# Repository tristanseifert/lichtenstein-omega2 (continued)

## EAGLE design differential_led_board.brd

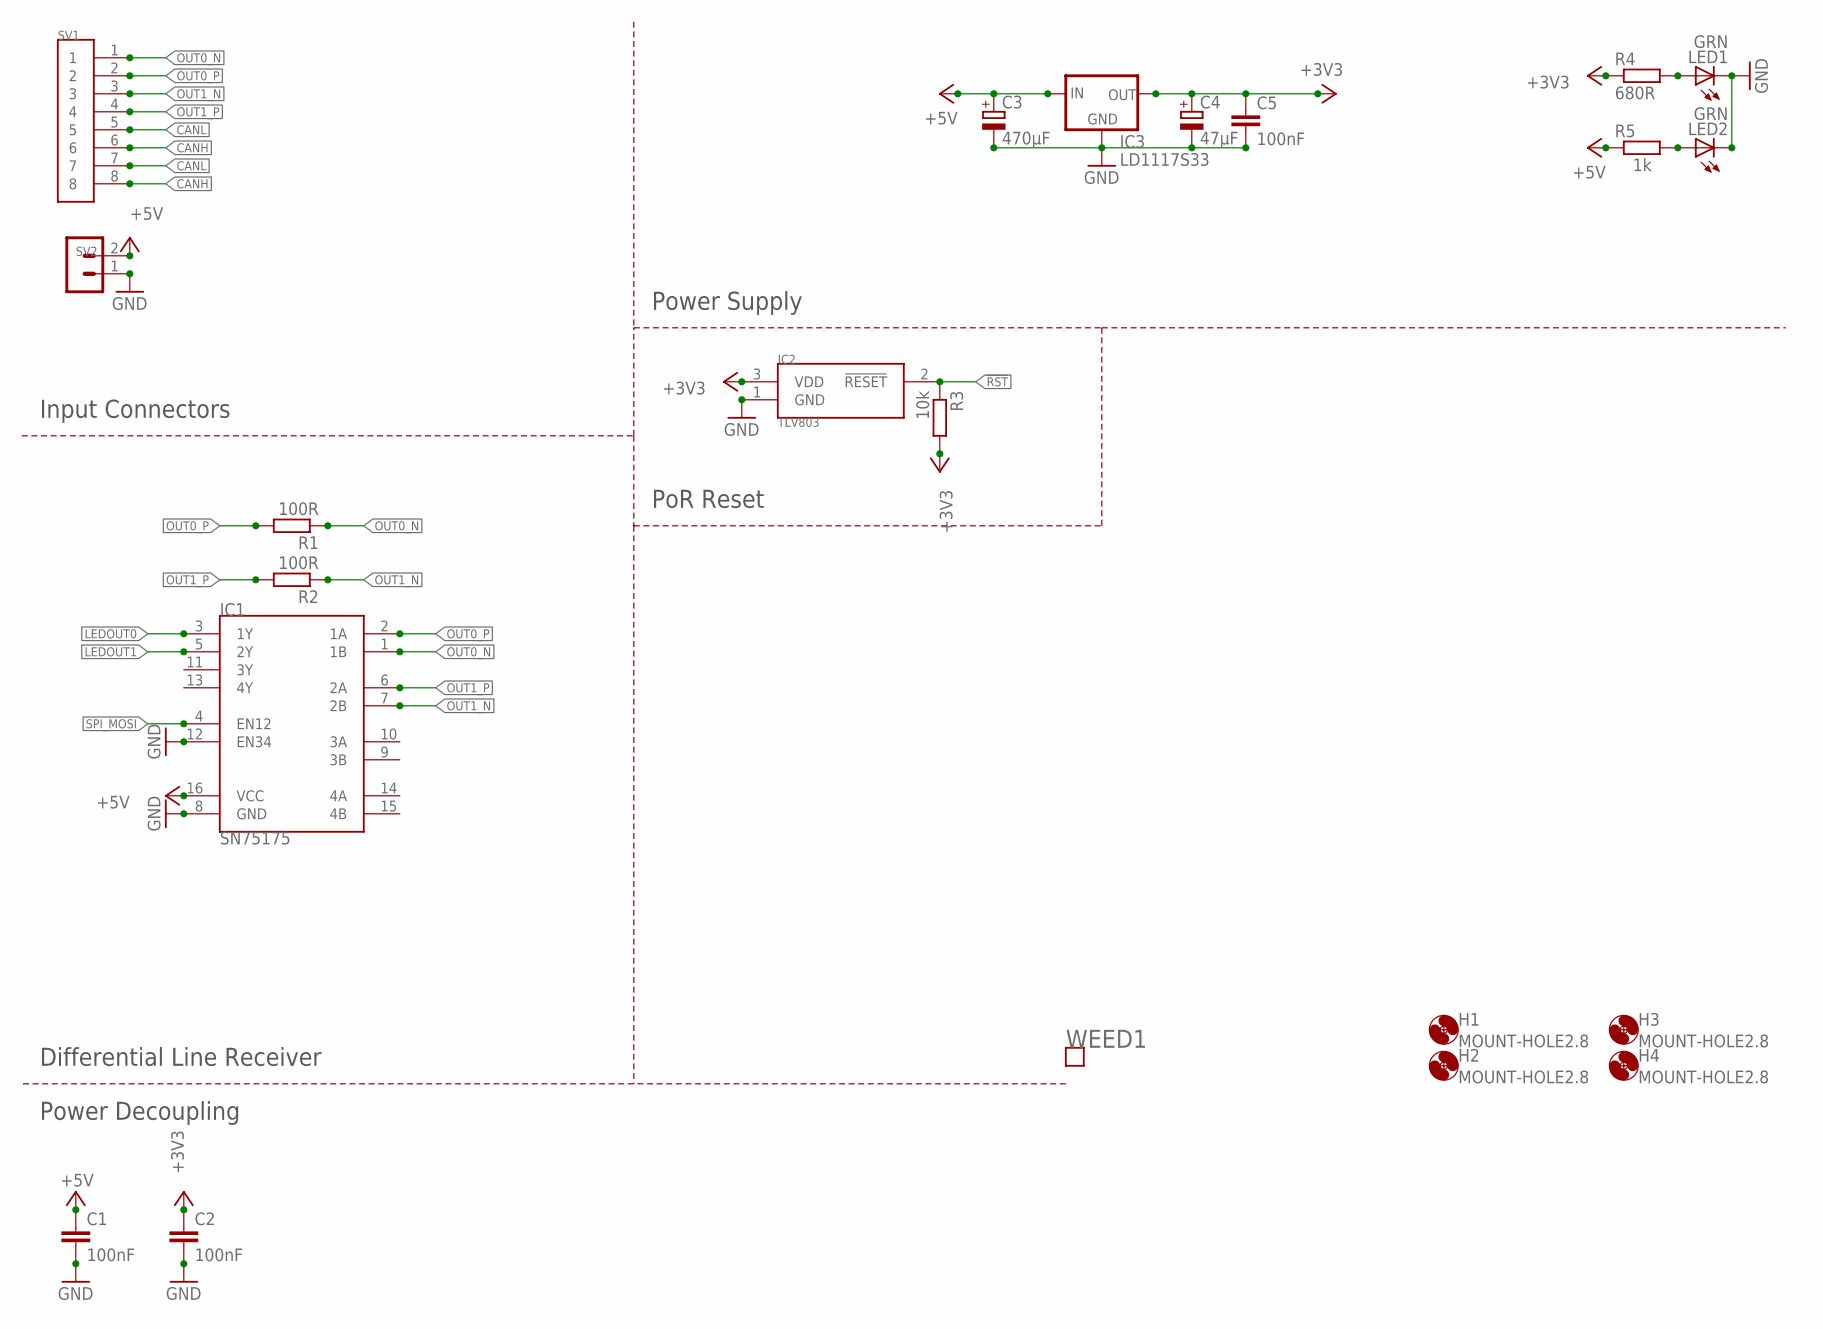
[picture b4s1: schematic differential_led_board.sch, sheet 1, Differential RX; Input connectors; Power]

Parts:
C1, C2, C5: 100nF; C0805; MOUSER 710-885012207072
C3: 470µF; UD-8X10_NICHICON; MOUSER 647-UWT1C471MNL1S
C4: 47µF; CT6032; MOUSER 581-TAJD476M016RNJV
H1, H2, H3, H4: MOUNT-HOLE2.8; 2,8
IC1: SN75175; SOP-16
IC2: TLV803; SOT23
IC3: LD1117S33; SOT223
LED1, LED2: GRN; CHIPLED_1206; MOUSER 604-APTR3216SGC
R1, R2: 100R; M1206; MOUSER 652-CR1206FX-1000ELF
R3: 10k; M0805; MOUSER 755-ESR10EZPJ103
R4: 680R; M0805; MOUSER 652-CR0805-FX6800GLF
R5: 1k; M0805; MOUSER 755-ESR10EZPJ102
SV1: SS-51000-003
SV2: 1792863
WEED1: WEED; DOINK

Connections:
!RST: IC2.2 (!RESET), R3.1; also elsewhere on the board
+3V3: C2.1, C4.+, C5.1, IC2.3 (VDD), IC3.2 (OUT), IC3.4 (OUT), R3.2, R4.1; also elsewhere on the board
+5V: C1.1, C3.+, IC1.16 (VCC), IC3.3 (IN), R5.1, SV2.2; also elsewhere on the board
CANH: SV1.6, SV1.8; also elsewhere on the board
CANL: SV1.5, SV1.7; also elsewhere on the board
GND: C1.2, C2.2, C3.-, C4.-, C5.2, IC1.8 (GND), IC1.12 (EN34), IC2.1 (GND), IC3.1 (GND), LED1.C, LED2.C, SV2.1; also elsewhere on the board
LEDOUT0: IC1.3 (1Y); also elsewhere on the board
LEDOUT1: IC1.5 (2Y); also elsewhere on the board
unnamed: LED1.A, R4.2
unnamed: LED2.A, R5.2
OUT0_N: IC1.1 (1B), R1.1, SV1.1
OUT0_P: IC1.2 (1A), R1.2, SV1.2
OUT1_N: IC1.7 (2B), R2.1, SV1.3
OUT1_P: IC1.6 (2A), R2.2, SV1.4
SPI_MOSI: IC1.4 (EN12); also elsewhere on the board

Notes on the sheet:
PoR Reset
Differential Line Receiver
Input Connectors
Power Supply
Power Decoupling

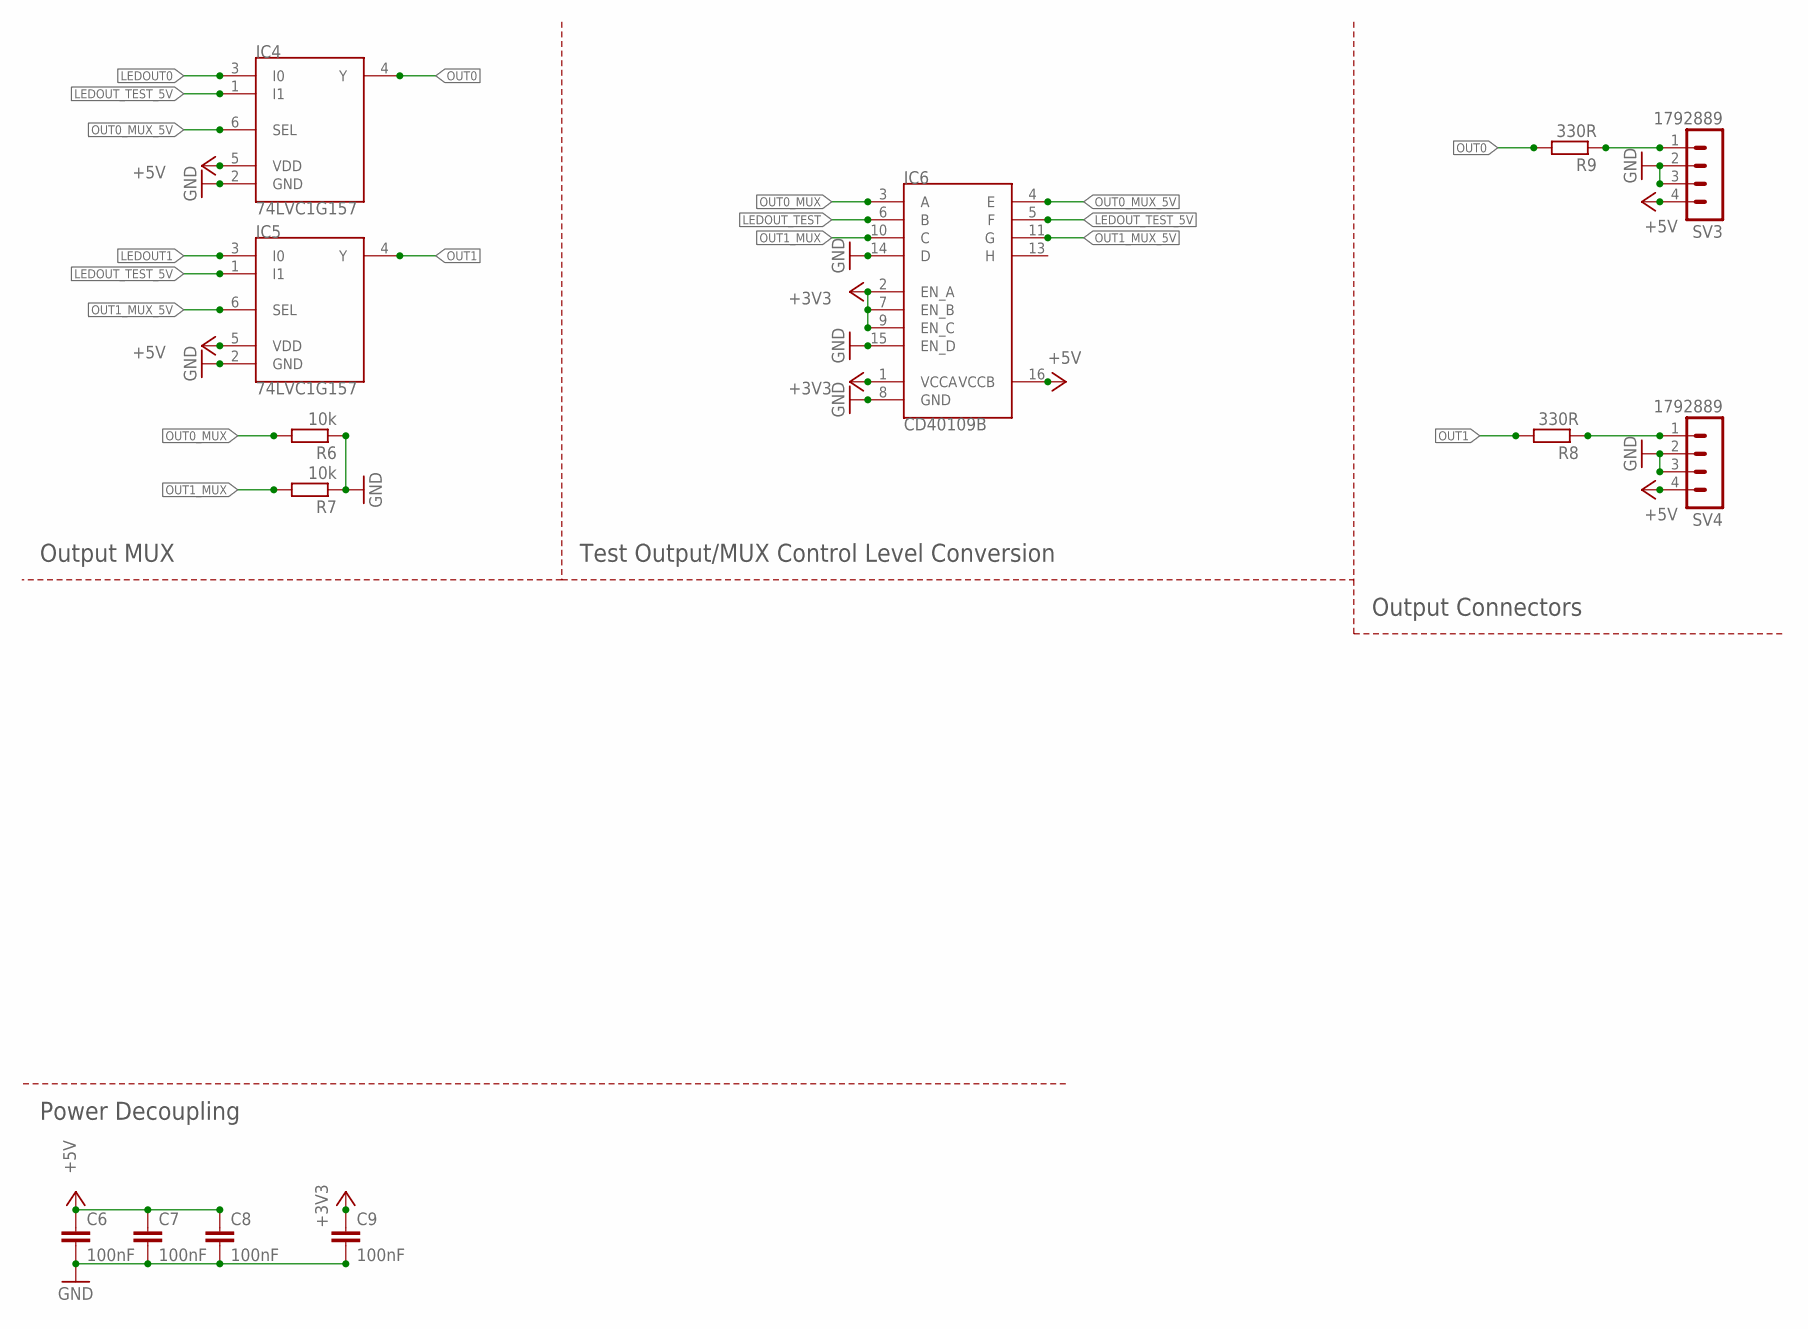
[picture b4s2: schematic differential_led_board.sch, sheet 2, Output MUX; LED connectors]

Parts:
C6, C7, C8, C9: 100nF; C0805; MOUSER 710-885012207072
IC4, IC5: 74LVC1G157; SOT457R_PHILIPS
IC6: CD40109B; SO16
R6, R7: 10k; M0805; MOUSER 755-ESR10EZPJ103
R8, R9: 330R; M0805; MOUSER 71-CRCW0805330RFKEAC
SV3, SV4: 1792889

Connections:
+3V3: C9.1, IC6.1 (VCCA), IC6.2 (EN_A), IC6.7 (EN_B), IC6.9 (EN_C); also elsewhere on the board
+5V: C6.1, C7.1, C8.1, IC4.5 (VDD), IC5.5 (VDD), IC6.16 (VCCB), SV3.4, SV4.4; also elsewhere on the board
GND: C6.2, C7.2, C8.2, C9.2, IC4.2 (GND), IC5.2 (GND), IC6.8 (GND), IC6.14 (D), IC6.15 (EN_D), R6.1, R7.1, SV3.2, SV3.3, SV4.2, SV4.3; also elsewhere on the board
LEDOUT0: IC4.3 (I0); also elsewhere on the board
LEDOUT1: IC5.3 (I0); also elsewhere on the board
LEDOUT_TEST: IC6.6 (B); also elsewhere on the board
LEDOUT_TEST_5V: IC4.1 (I1), IC5.1 (I1), IC6.5 (F)
unnamed: R8.1, SV4.1
unnamed: R9.1, SV3.1
OUT0: IC4.4 (Y), R9.2
OUT0_MUX: IC6.3 (A), R6.2; also elsewhere on the board
OUT0_MUX_5V: IC4.6 (SEL), IC6.4 (E)
OUT1: IC5.4 (Y), R8.2
OUT1_MUX: IC6.10 (C), R7.2; also elsewhere on the board
OUT1_MUX_5V: IC5.6 (SEL), IC6.11 (G)

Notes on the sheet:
Power Decoupling
Output Connectors
Output MUX
Test Output/MUX Control Level Conversion

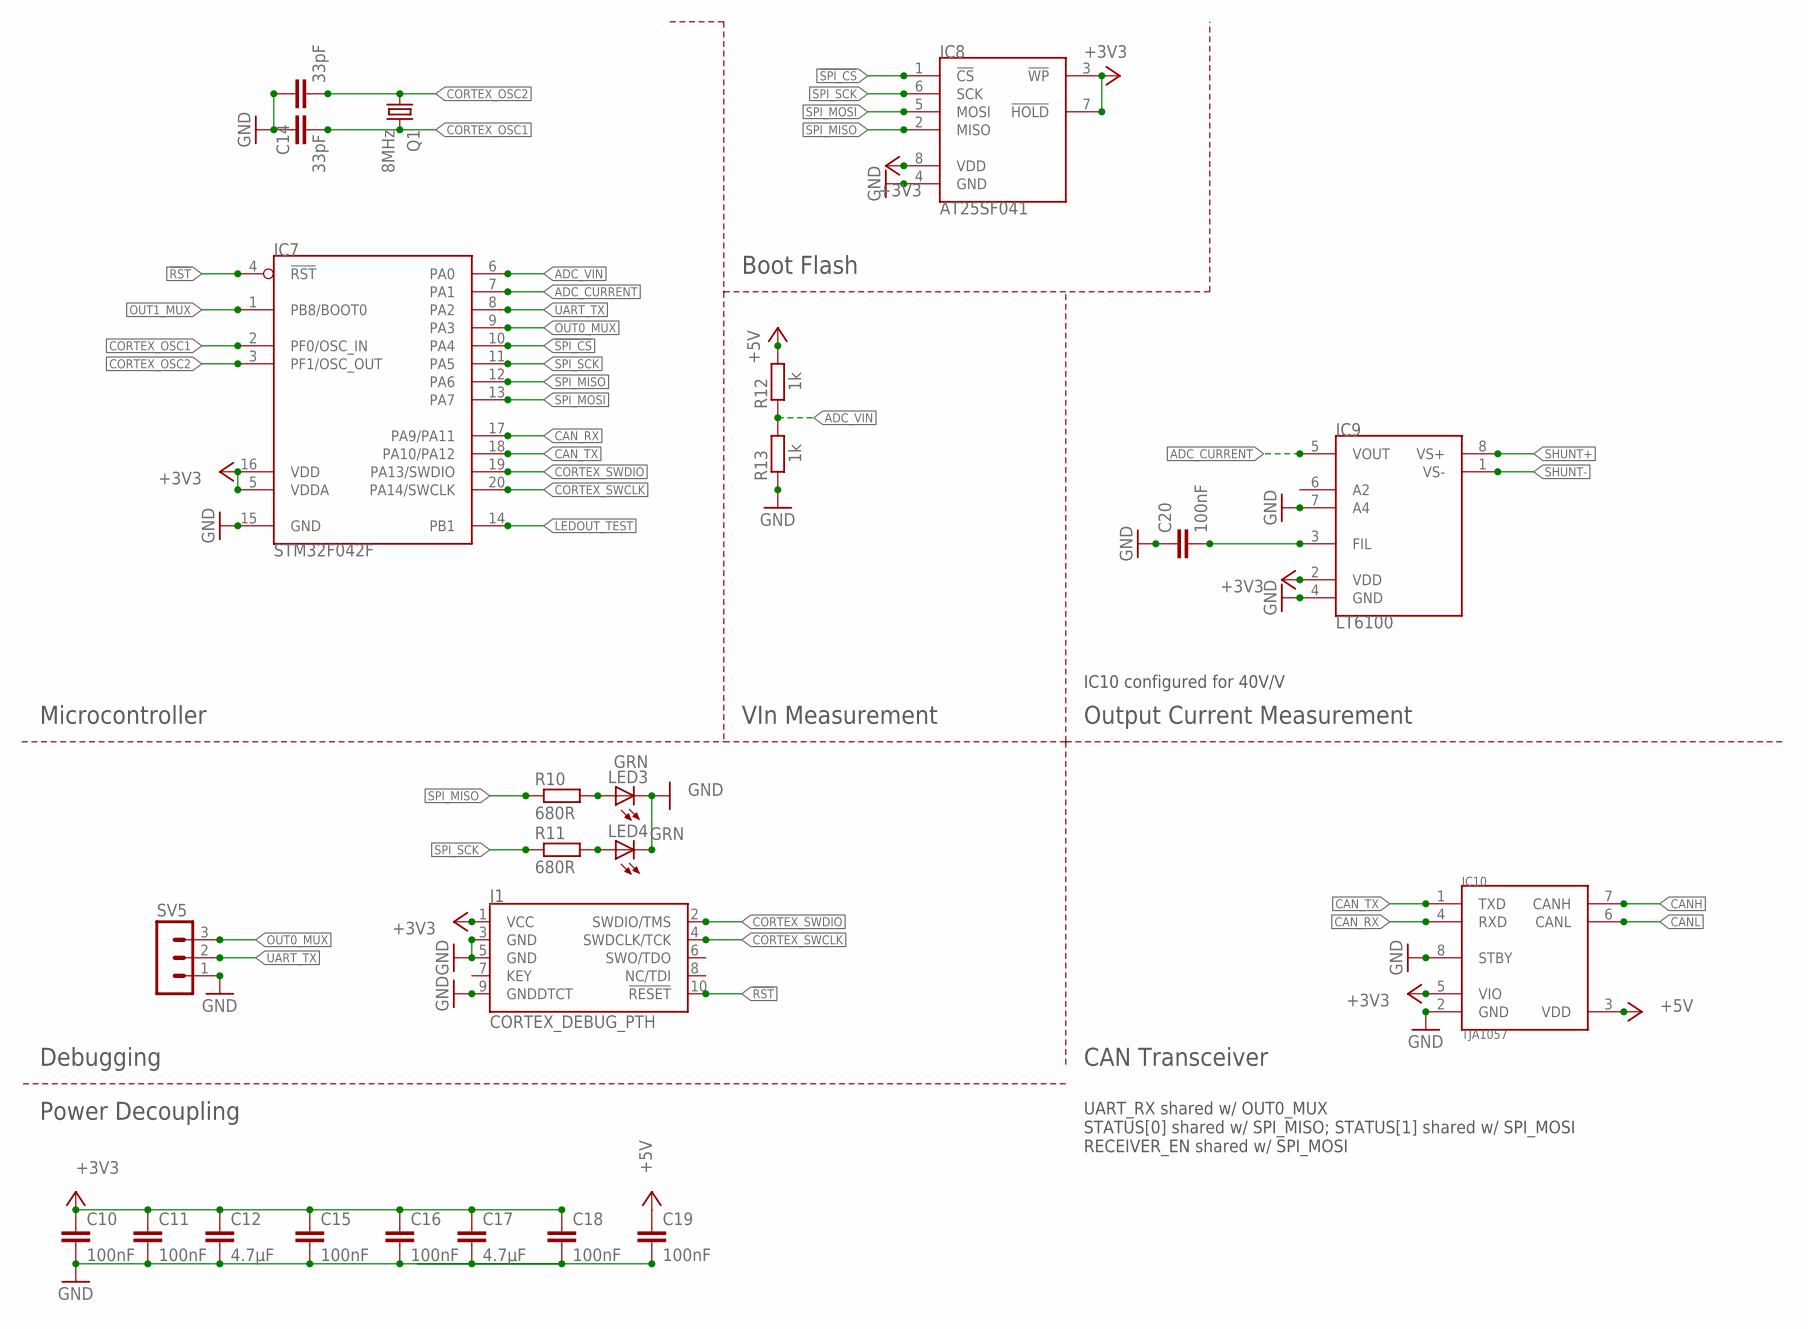
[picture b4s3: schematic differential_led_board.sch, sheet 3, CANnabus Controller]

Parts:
C10, C11, C15, C16, C18, C19: 100nF; C0805; MOUSER 710-885012207072
C12, C17: 4.7µF; C0805; MOUSER 81-GRM21BR71A475ME1L
C13, C14: 33pF; C0805; MOUSER 710-885012007013
C20: 100nF; C0805; MOUSER 710-885012007059
IC7: STM32F042F; TSSOP20
IC8: AT25SF041; SOIC8
IC9: LT6100; MSOP8
IC10: TJA1057; SOIC8
J1: CORTEX_DEBUG_PTH; 2X5-PTH-1.27MM
LED3, LED4: GRN; CHIPLED_1206; MOUSER 604-APTR3216SGC
Q1: 8MHz; HC49UP; MOUSER 449-LFXTAL030234REEL
R10, R11: 680R; M0805; MOUSER 652-CR0805-FX6800GLF
R12, R13: 1k; M0805; MOUSER 755-ESR10EZPJ102
SV5: MA03-1

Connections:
!RST: IC7.4 (!RST), J1.10 (!RESET); also elsewhere on the board
!SPI_CS: IC7.10 (PA4), IC8.1 (!CS)
+3V3: C10.1, C11.1, C12.1, C15.1, C16.1, C17.1, C18.1, IC7.5 (VDDA), IC7.16 (VDD), IC8.3 (!WP), IC8.7 (!HOLD), IC8.8 (VDD), IC9.2 (VDD), IC10.5 (VIO), J1.1 (VCC); also elsewhere on the board
+5V: C19.1, IC10.3 (VDD), R12.2; also elsewhere on the board
ADC_CURRENT: IC7.7 (PA1), IC9.5 (VOUT)
ADC_VIN: IC7.6 (PA0), R12.1, R13.2
CANH: IC10.7 (CANH); also elsewhere on the board
CANL: IC10.6 (CANL); also elsewhere on the board
CAN_RX: IC7.17 (PA9/PA11), IC10.4 (RXD)
CAN_TX: IC7.18 (PA10/PA12), IC10.1 (TXD)
CORTEX_OSC1: C14.2, IC7.2 (PF0/OSC_IN), Q1.2
CORTEX_OSC2: C13.2, IC7.3 (PF1/OSC_OUT), Q1.1
CORTEX_SWCLK: IC7.20 (PA14/SWCLK), J1.4 (SWDCLK/TCK)
CORTEX_SWDIO: IC7.19 (PA13/SWDIO), J1.2 (SWDIO/TMS)
GND: C10.2, C11.2, C12.2, C13.1, C14.1, C15.2, C16.2, C17.2, C18.2, C19.2, C20.1, IC7.15 (GND), IC8.4 (GND), IC9.4 (GND), IC9.7 (A4), IC10.2 (GND), IC10.8 (STBY), J1.3 (GND), J1.5 (GND), J1.9 (GNDDTCT), LED3.C, LED4.C, R13.1, SV5.1; also elsewhere on the board
LEDOUT_TEST: IC7.14 (PB1); also elsewhere on the board
unnamed: LED3.A, R10.2
unnamed: LED4.A, R11.2
unnamed: C20.2, IC9.3 (FIL)
OUT0_MUX: IC7.9 (PA3), SV5.3; also elsewhere on the board
OUT1_MUX: IC7.1 (PB8/BOOT0); also elsewhere on the board
SHUNT+: IC9.8 (VS+)
SHUNT-: IC9.1 (VS-)
SPI_MISO: IC7.12 (PA6), IC8.2 (MISO), R10.1
SPI_MOSI: IC7.13 (PA7), IC8.5 (MOSI); also elsewhere on the board
SPI_SCK: IC7.11 (PA5), IC8.6 (SCK), R11.1
UART_TX: IC7.8 (PA2), SV5.2

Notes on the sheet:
UART_RX shared w/ OUT0_MUX STATUS[0] shared w/ SPI_MISO; STATUS[1] shared w/ SPI_MOSI RECEIVER_EN shared w/ SPI_MOSI
Microcontroller
Debugging
Power Decoupling
CAN Transceiver
Boot Flash
VIn Measurement
Output Current Measurement
IC10 configured for 40V/V

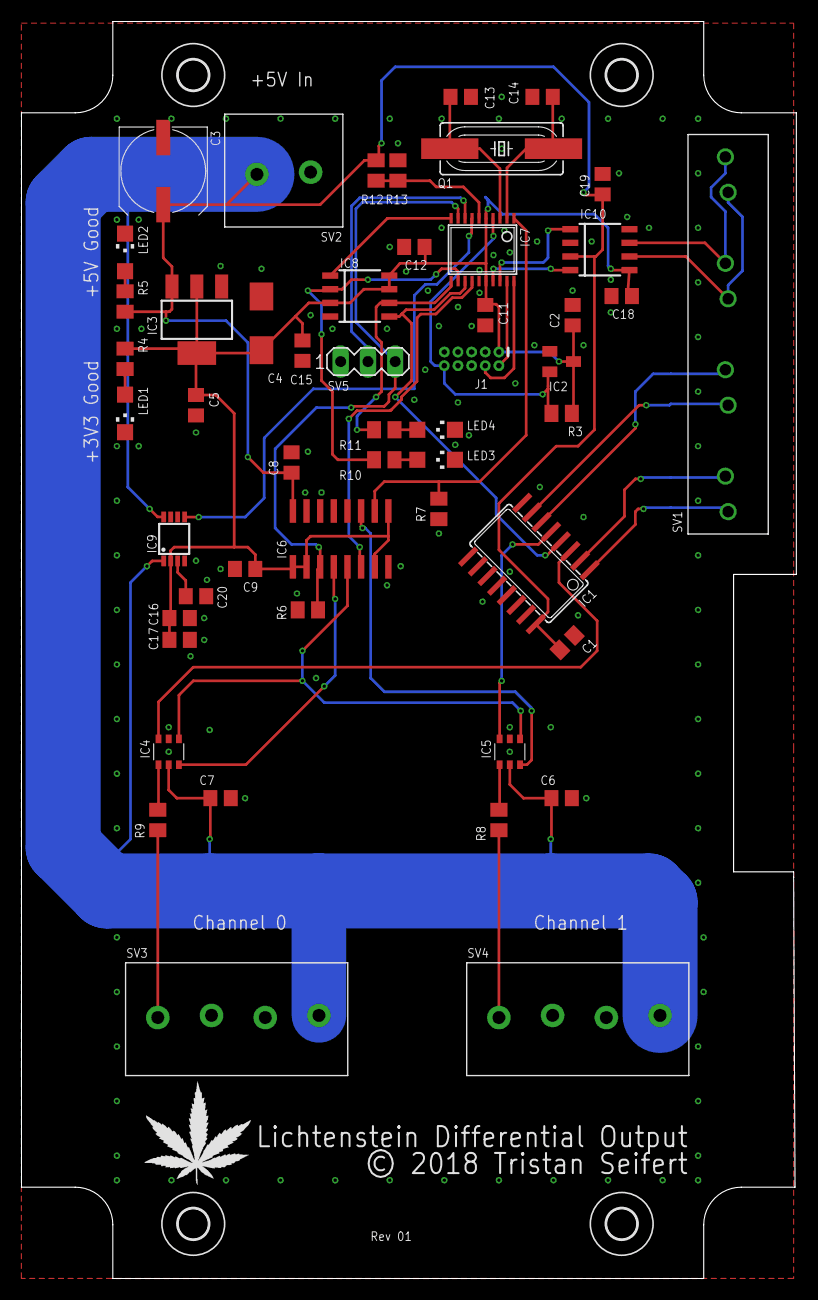
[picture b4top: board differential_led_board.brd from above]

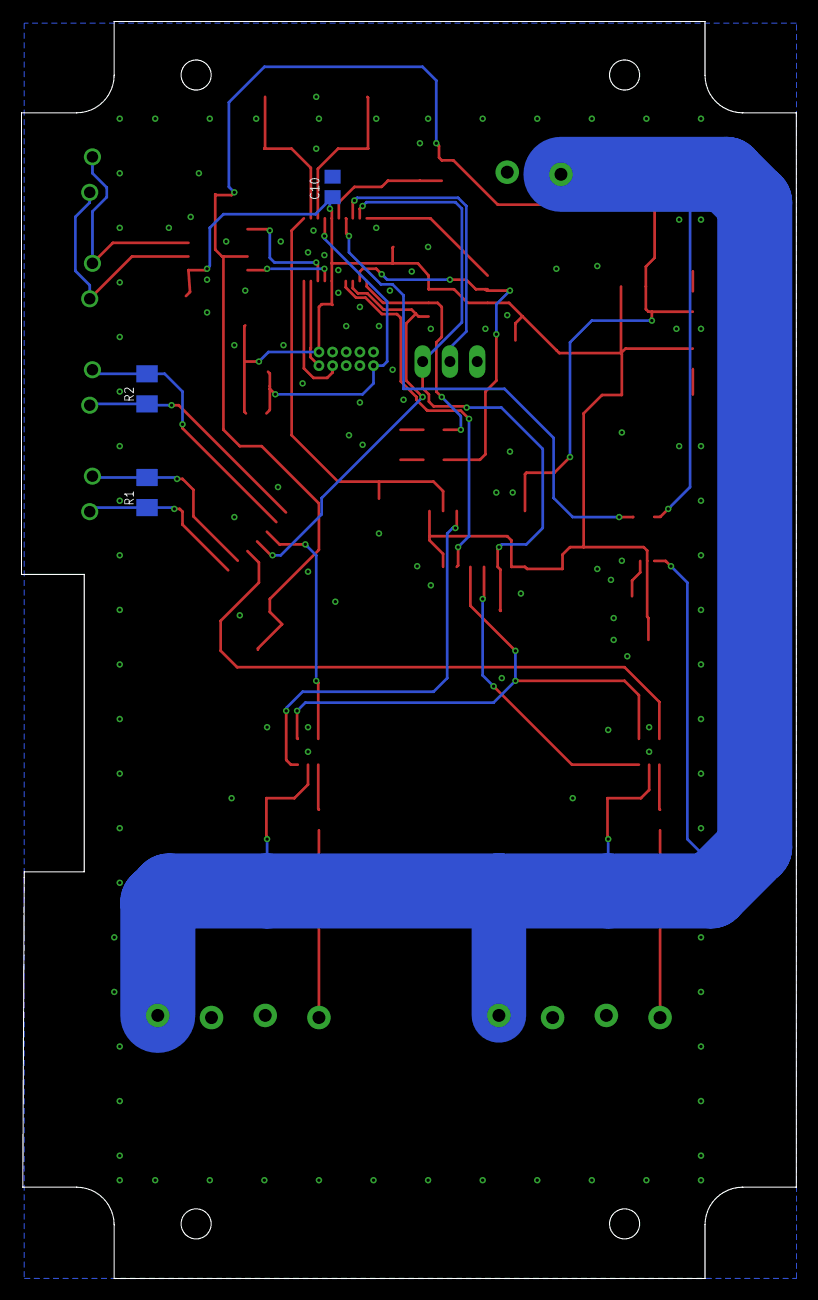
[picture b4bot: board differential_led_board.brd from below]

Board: 2 copper layers, 72.1 x 117.0 mm, 59 parts (3 on the bottom side), 40 nets.

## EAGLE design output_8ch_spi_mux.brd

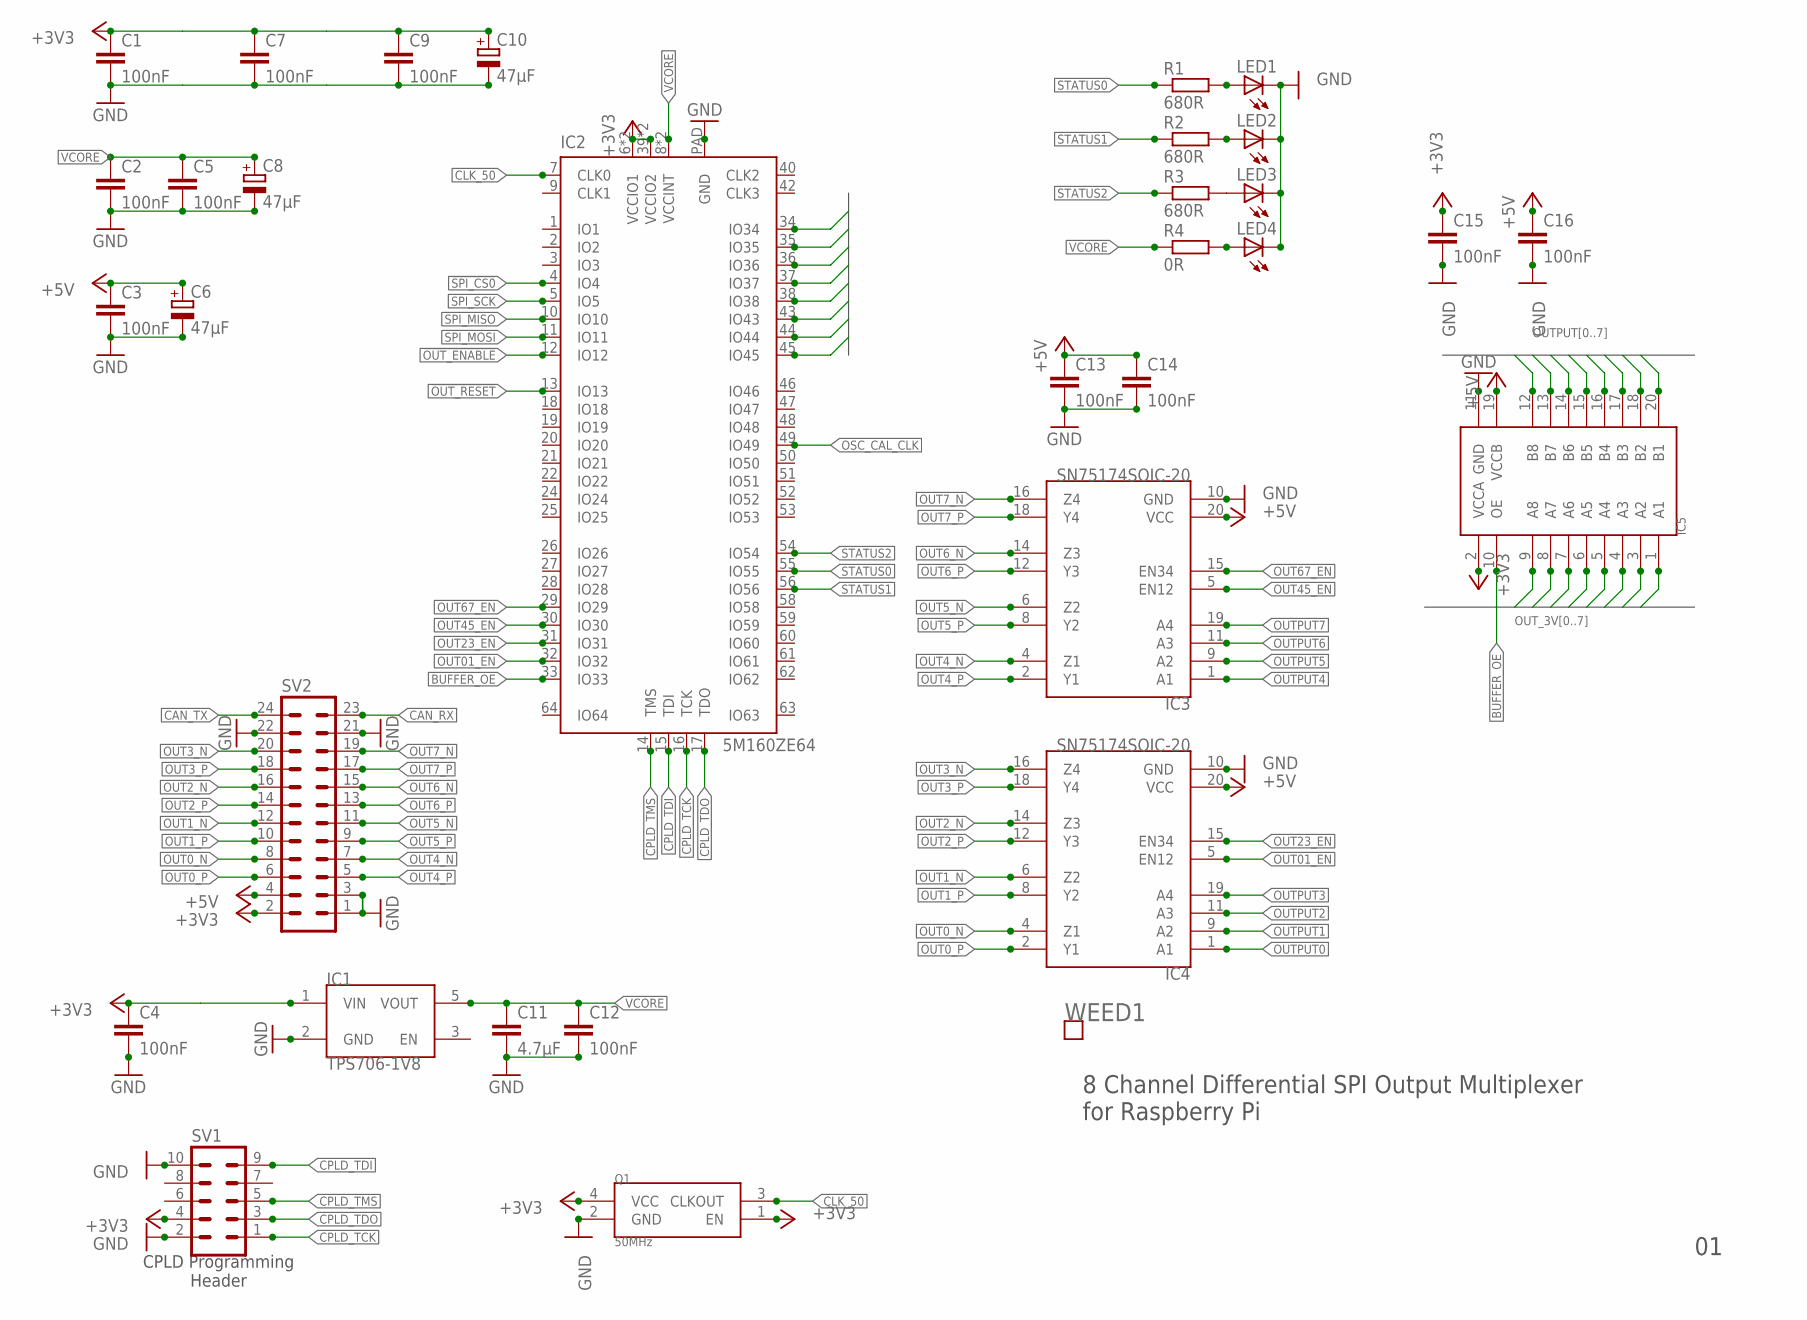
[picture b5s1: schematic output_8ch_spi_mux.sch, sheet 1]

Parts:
C1, C2, C3, C4, C5, C7, C9, C12, C13, C14, C15, C16: 100nF; C0805; MOUSER 710-885012207072
C6, C8, C10: 47µF; CT6032; MOUSER 581-TAJD476M016RNJV
C11: 4.7µF; C0805; MOUSER 81-GRM21BR71A475ME1L
IC1: TPS706-1V8; SOT23-5
IC2: 5M160ZE64; EQFP64
IC3, IC4: SN75174SOIC-20; SOIC20S
IC5: TXB0108TSSOP20; TSSOP20
LED1, LED2, LED3: LEDCHIPLED_1206; CHIPLED_1206; MOUSER 604-APTR3216SGC
LED4: LEDCHIPLED_1206; CHIPLED_1206; MOUSER 604-APT3216LSECKJ3RV
Q1: 50MHz; VLGA-4; MOUSER 579-6101JI2A0500000T
R1, R2, R3: 680R; M0805; MOUSER 652-CR0805-FX6800GLF
R4: 0R; M0805; MOUSER 71-RCG08050000Z0EA
SV1: MA05-2; MOUSER 517-30310-6002
SV2: MA12-2; MOUSER 517-30320-6002
WEED1: WEED; DOINK

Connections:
!OUT_ENABLE: IC2.12 (IO12); also elsewhere on the board
!OUT_RESET: IC2.13 (IO13); also elsewhere on the board
!SPI_CS0: IC2.4 (IO4); also elsewhere on the board
+3V3: C1.1, C4.1, C7.1, C9.1, C10.+, C15.1, IC1.1 (VIN), IC2.6 (VCCIO1), IC2.23 (VCCIO1), IC2.39 (VCCIO2), IC2.57 (VCCIO2), IC5.2 (VCCA), Q1.1 (EN), Q1.4 (VCC), SV1.4, SV2.2; also elsewhere on the board
+5V: C3.1, C6.+, C13.1, C14.1, C16.1, IC3.20 (VCC), IC4.20 (VCC), IC5.19 (VCCB), SV2.4; also elsewhere on the board
BUFFER_OE: IC2.33 (IO33), IC5.10 (OE)
CAN_RX: SV2.23; also elsewhere on the board
CAN_TX: SV2.24; also elsewhere on the board
CLK_50: IC2.7 (CLK0), Q1.3 (CLKOUT)
CPLD_TCK: IC2.16 (TCK), SV1.1
CPLD_TDI: IC2.15 (TDI), SV1.9
CPLD_TDO: IC2.17 (TDO), SV1.3
CPLD_TMS: IC2.14 (TMS), SV1.5
GND: C1.2, C2.2, C3.2, C4.2, C5.2, C6.-, C7.2, C8.-, C9.2, C10.-, C11.2, C12.2, C13.2, C14.2, C15.2, C16.2, IC1.2 (GND), IC2.PAD (GND), IC3.10 (GND), IC4.10 (GND), IC5.11 (GND), LED1.C, LED2.C, LED3.C, LED4.C, Q1.2 (GND), SV1.2, SV1.10, SV2.1, SV2.3, SV2.21, SV2.22; also elsewhere on the board
unnamed: LED4.A, R4.2
unnamed: LED3.A, R3.2
unnamed: LED1.A, R1.2
unnamed: LED2.A, R2.2
OSC_CAL_CLK: IC2.49 (IO49); also elsewhere on the board
OUT0_N: IC4.4 (Z1), SV2.8
OUT0_P: IC4.2 (Y1), SV2.6
OUT01_EN: IC2.32 (IO32), IC4.5 (EN12)
OUT1_N: IC4.6 (Z2), SV2.12
OUT1_P: IC4.8 (Y2), SV2.10
OUT2_N: IC4.14 (Z3), SV2.16
OUT2_P: IC4.12 (Y3), SV2.14
OUT3_N: IC4.16 (Z4), SV2.20
OUT3_P: IC4.18 (Y4), SV2.18
OUT4_N: IC3.4 (Z1), SV2.7
OUT4_P: IC3.2 (Y1), SV2.5
OUT5_N: IC3.6 (Z2), SV2.11
OUT5_P: IC3.8 (Y2), SV2.9
OUT6_N: IC3.14 (Z3), SV2.15
OUT6_P: IC3.12 (Y3), SV2.13
OUT7_N: IC3.16 (Z4), SV2.19
OUT7_P: IC3.18 (Y4), SV2.17
OUT23_EN: IC2.31 (IO31), IC4.15 (EN34)
OUT45_EN: IC2.30 (IO30), IC3.5 (EN12)
OUT67_EN: IC2.29 (IO29), IC3.15 (EN34)
OUTPUT0: IC4.1 (A1), IC5.20 (B1)
OUTPUT1: IC4.9 (A2), IC5.18 (B2)
OUTPUT2: IC4.11 (A3), IC5.17 (B3)
OUTPUT3: IC4.19 (A4), IC5.16 (B4)
OUTPUT4: IC3.1 (A1), IC5.15 (B5)
OUTPUT5: IC3.9 (A2), IC5.14 (B6)
OUTPUT6: IC3.11 (A3), IC5.13 (B7)
OUTPUT7: IC3.19 (A4), IC5.12 (B8)
OUT_3V0: IC2.45 (IO45), IC5.1 (A1)
OUT_3V1: IC2.44 (IO44), IC5.3 (A2)
OUT_3V2: IC2.43 (IO43), IC5.4 (A3)
OUT_3V3: IC2.38 (IO38), IC5.5 (A4)
OUT_3V4: IC2.37 (IO37), IC5.6 (A5)
OUT_3V5: IC2.36 (IO36), IC5.7 (A6)
OUT_3V6: IC2.35 (IO35), IC5.8 (A7)
OUT_3V7: IC2.34 (IO34), IC5.9 (A8)
SPI_MISO: IC2.10 (IO10); also elsewhere on the board
SPI_MOSI: IC2.11 (IO11); also elsewhere on the board
SPI_SCK: IC2.5 (IO5); also elsewhere on the board
STATUS0: IC2.55 (IO55), R1.1
STATUS1: IC2.56 (IO56), R2.1
STATUS2: IC2.54 (IO54), R3.1
VCORE: C2.1, C5.1, C8.+, C11.1, C12.1, IC1.5 (VOUT), IC2.8 (VCCINT), IC2.41 (VCCINT), R4.1

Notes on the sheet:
CPLD Programming Header
8 Channel Differential SPI Output Multiplexer for Raspberry Pi

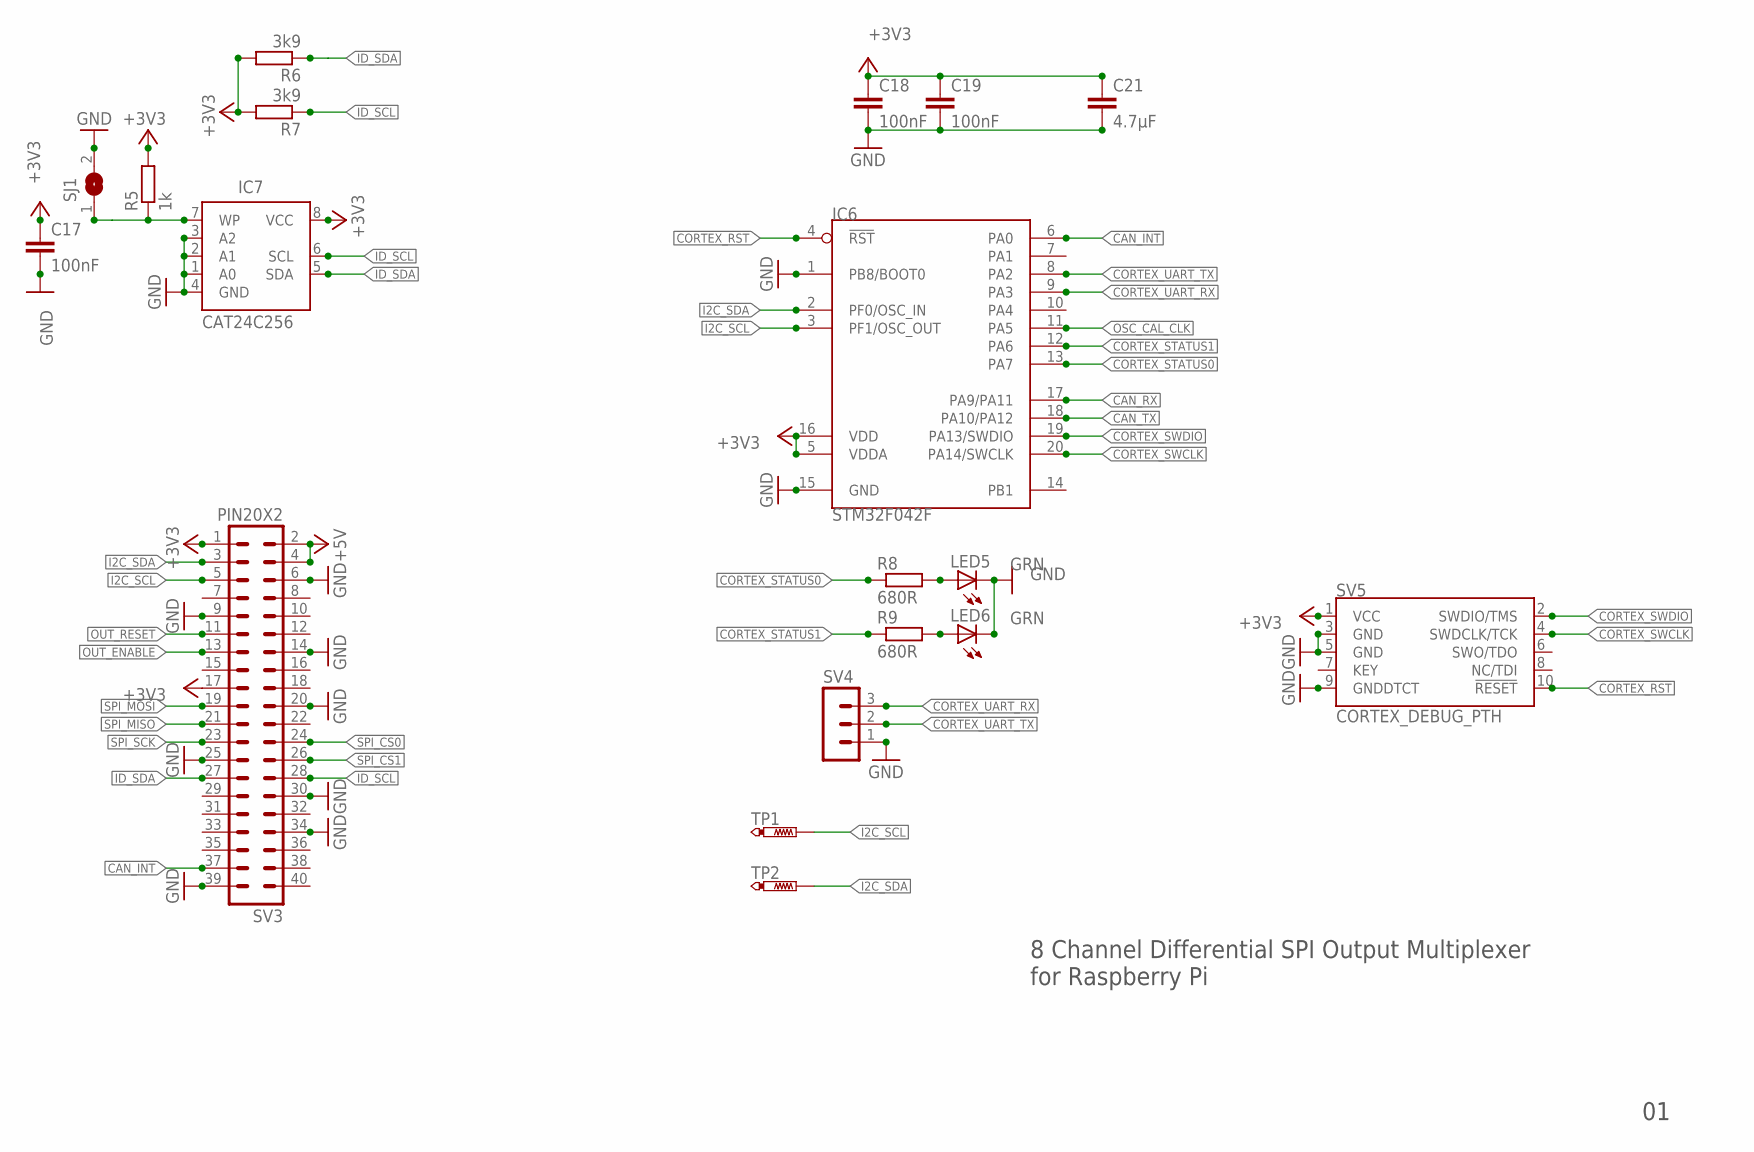
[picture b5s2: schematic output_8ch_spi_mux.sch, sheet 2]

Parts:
C17, C18, C19: 100nF; C0805; MOUSER 710-885012207072
C21: 4.7µF; C0805; MOUSER 81-GRM21BR71A475ME1L
IC6: STM32F042F; TSSOP20
IC7: CAT24C256; SOIC8; MOUSER 698-CAT24C256WI-GT3
LED5, LED6: GRN; CHIPLED_1206; MOUSER 604-APTR3216SGC
R5: 1k; M0805; MOUSER 667-ERJ-6ENF1001V
R6, R7: 3k9; M0805; MOUSER 667-ERJ-6ENF3901V
R8, R9: 680R; M0805; MOUSER 652-CR0805-FX6800GLF
SJ1: SJ
SV3: PIN20X2; PIN_20X2
SV4: MA03-1
SV5: CORTEX_DEBUG_PTH; 2X5-PTH-1.27MM
TP1, TP2: PTR1B1,27; B1,27

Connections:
!CAN_INT: IC6.6 (PA0), SV3.37
!CORTEX_RST: IC6.4 (!RST), SV5.10 (!RESET)
!OUT_ENABLE: SV3.13; also elsewhere on the board
!OUT_RESET: SV3.11; also elsewhere on the board
!SPI_CS0: SV3.24; also elsewhere on the board
!SPI_CS1: SV3.26
+3V3: C17.1, C18.1, C19.1, C21.1, IC6.5 (VDDA), IC6.16 (VDD), IC7.8 (VCC), R5.2, R6.2, R7.2, SV3.1, SV3.17, SV5.1 (VCC); also elsewhere on the board
+5V: SV3.2, SV3.4; also elsewhere on the board
CAN_RX: IC6.17 (PA9/PA11); also elsewhere on the board
CAN_TX: IC6.18 (PA10/PA12); also elsewhere on the board
CORTEX_STATUS0: IC6.13 (PA7), R8.1
CORTEX_STATUS1: IC6.12 (PA6), R9.1
CORTEX_SWCLK: IC6.20 (PA14/SWCLK), SV5.4 (SWDCLK/TCK)
CORTEX_SWDIO: IC6.19 (PA13/SWDIO), SV5.2 (SWDIO/TMS)
CORTEX_UART_RX: IC6.9 (PA3), SV4.3
CORTEX_UART_TX: IC6.8 (PA2), SV4.2
GND: C17.2, C18.2, C19.2, C21.2, IC6.1 (PB8/BOOT0), IC6.15 (GND), IC7.1 (A0), IC7.2 (A1), IC7.3 (A2), IC7.4 (GND), LED5.C, LED6.C, SJ1.2, SV3.6, SV3.9, SV3.14, SV3.20, SV3.25, SV3.30, SV3.34, SV3.39, SV4.1, SV5.3 (GND), SV5.5 (GND), SV5.9 (GNDDTCT); also elsewhere on the board
I2C_SCL: IC6.3 (PF1/OSC_OUT), SV3.5, TP1.TP
I2C_SDA: IC6.2 (PF0/OSC_IN), SV3.3, TP2.TP
ID_SCL: IC7.6 (SCL), R7.1, SV3.28
ID_SDA: IC7.5 (SDA), R6.1, SV3.27
unnamed: IC7.7 (WP), R5.1, SJ1.1
unnamed: LED5.A, R8.2
unnamed: LED6.A, R9.2
OSC_CAL_CLK: IC6.11 (PA5); also elsewhere on the board
SPI_MISO: SV3.21; also elsewhere on the board
SPI_MOSI: SV3.19; also elsewhere on the board
SPI_SCK: SV3.23; also elsewhere on the board

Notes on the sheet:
8 Channel Differential SPI Output Multiplexer for Raspberry Pi

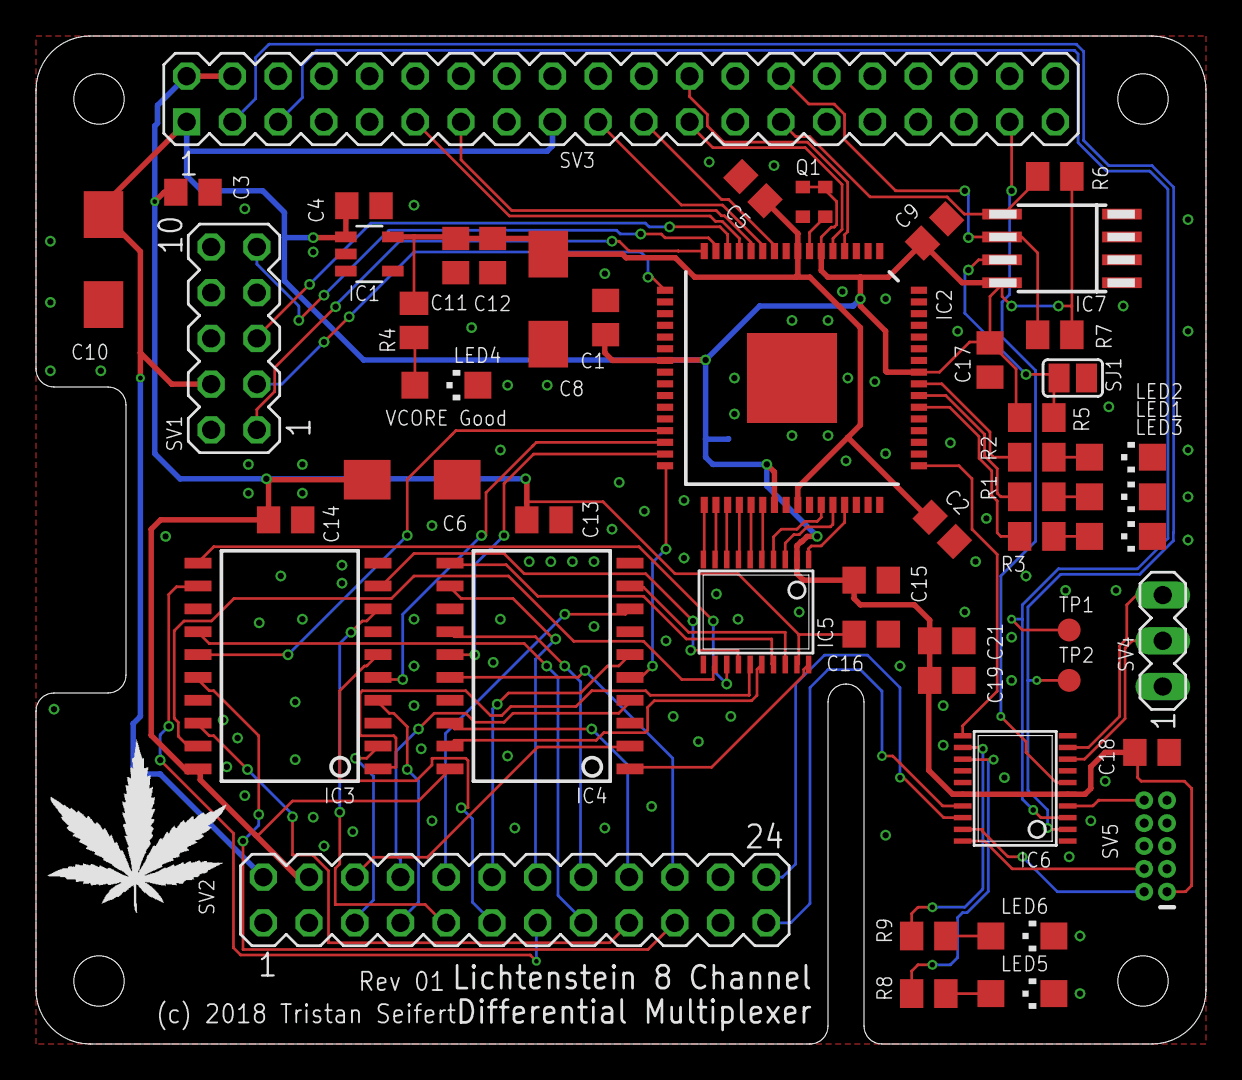
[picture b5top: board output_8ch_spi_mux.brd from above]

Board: 2 copper layers, 65.0 x 56.0 mm, 52 parts (1 on the bottom side), 77 nets.
